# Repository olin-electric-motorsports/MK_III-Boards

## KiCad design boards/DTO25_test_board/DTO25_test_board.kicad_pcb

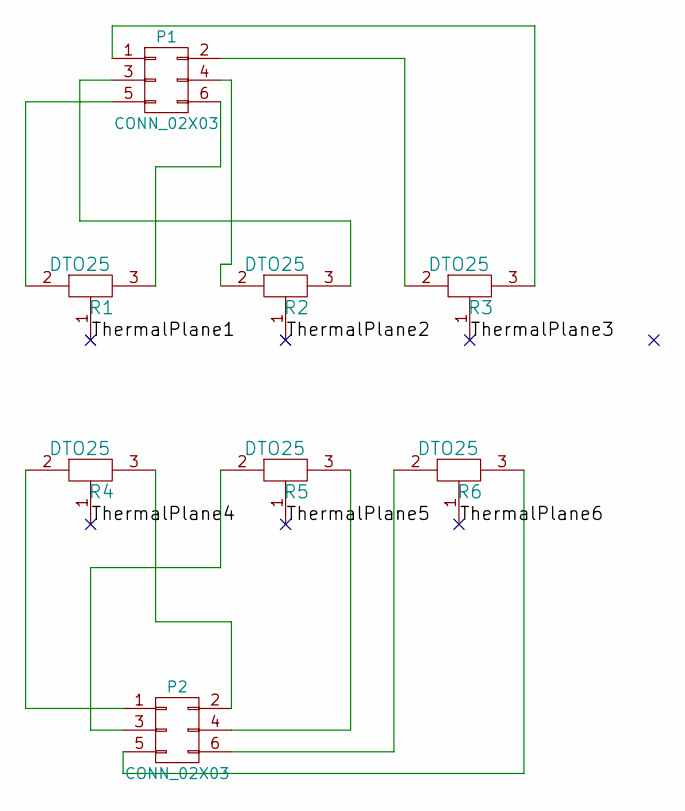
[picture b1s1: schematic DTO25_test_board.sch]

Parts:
P1, P2: CONN_02X03; Pin_Header_Straight_2x03; MPN 609-3234-ND
R1, R2, R3, R4, R5, R6: DTO25

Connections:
/ThermalPlane1: R1.1
/ThermalPlane2: R2.1
/ThermalPlane3: R3.1
/ThermalPlane4: R4.1
/ThermalPlane5: R5.1
/ThermalPlane6: R6.1
unnamed: P1.1, R3.3
unnamed: P1.2, R3.2
unnamed: P1.3, R2.3
unnamed: P1.4, R2.2
unnamed: P1.5, R1.2
unnamed: P1.6, R1.3
unnamed: P2.1, R4.2
unnamed: P2.2, R4.3
unnamed: P2.3, R5.2
unnamed: P2.4, R5.3
unnamed: P2.5, R6.3
unnamed: P2.6, R6.2

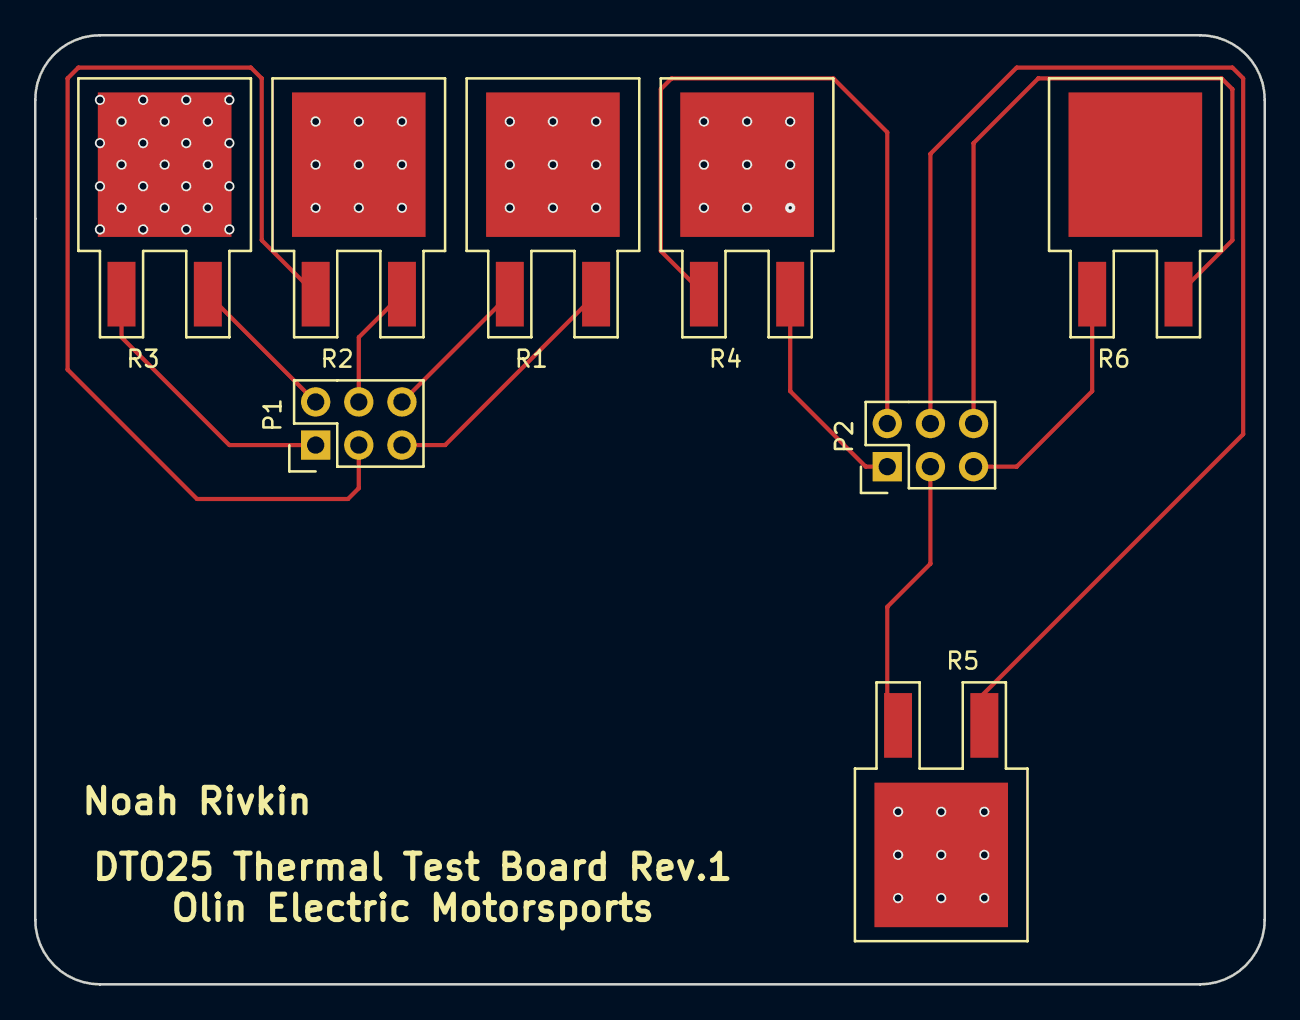
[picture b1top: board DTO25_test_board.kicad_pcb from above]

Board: 2 copper layers, 72.4 x 55.9 mm, 8 parts (0 on the bottom side), 12 nets.

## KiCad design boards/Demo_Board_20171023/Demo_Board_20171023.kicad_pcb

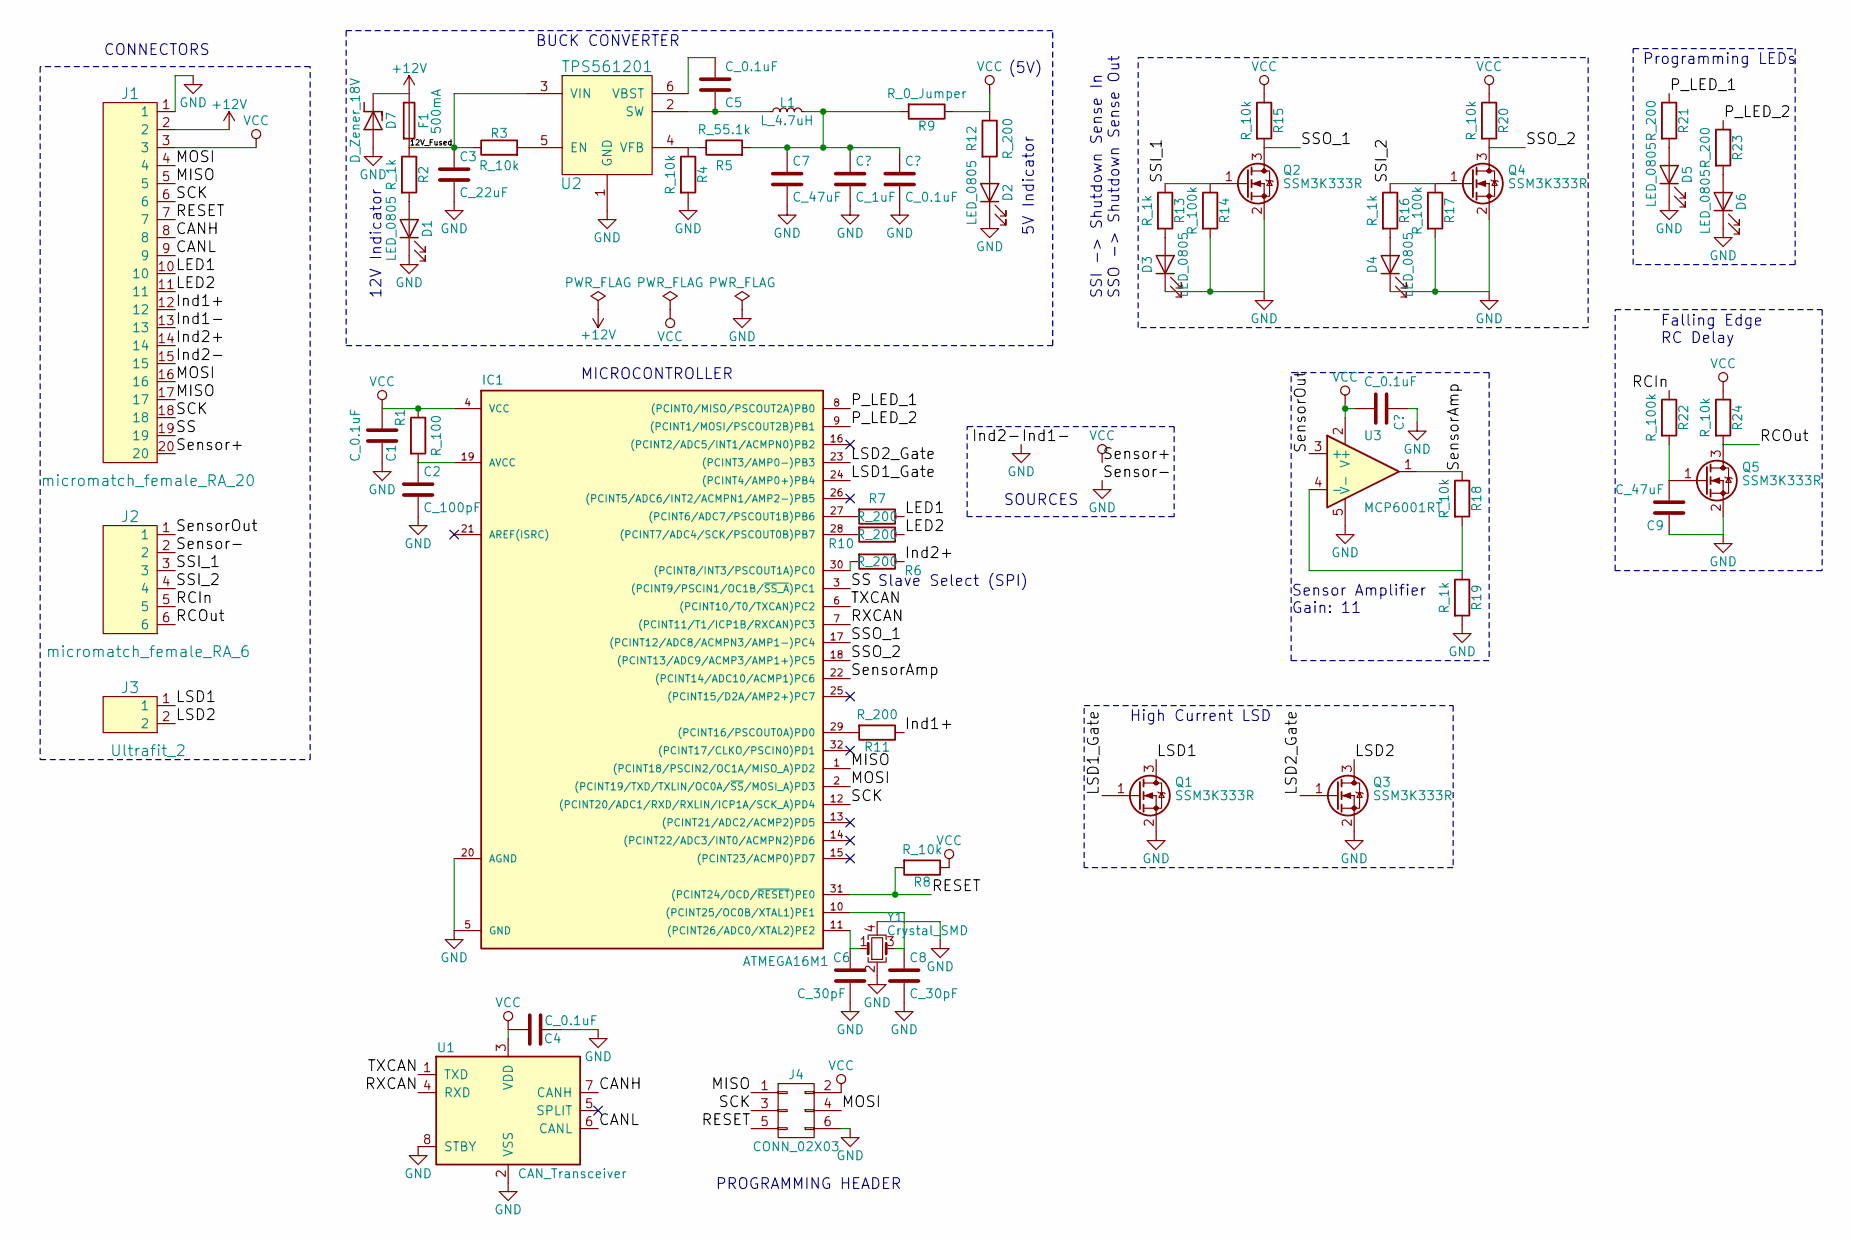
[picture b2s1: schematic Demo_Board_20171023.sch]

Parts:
C1, C4, C5: C_0.1uF; C_0805_OEM; MPN 478-3352-1-ND
C2: C_100pF; C_0805_OEM; MPN 399-1122-1-ND
C3: C_22uF; C_1206_OEM; MPN 1276-2725-1-ND
C6, C8: C_30pF; C_0805_OEM; MPN 1276-1130-1-ND
C7, C9: C_47uF; C_0805_OEM; MPN 587-4280-1-ND
D1, D2, D3, D4, D5, D6: LED_0805; LED_0805_OEM; MPN 475-1410-1-ND
D7: D_Zener_18V; DO-214AA; MPN SMBJ5355B-TPMSCT-ND
F1: 500mA; Fuse_1210; MPN 507-1786-1-ND
IC1: ATMEGA16M1; TQFP-32_7x7mm_Pitch0.8mm; MPN ATMEGA16M1-AU-ND
J1: micromatch_female_RA_20; micromatch_female_ra_20; MPN A99490CT-ND
J2: micromatch_female_RA_6; micromatch_female_ra_6; MPN A99483CT-ND
J3: Ultrafit_2; MPN WM11570-ND
J4: CONN_02X03; Pin_Header_Straight_2x03; MPN 609-3234-ND
L1: L_4.7uH; 4.7uH_Inductor_OEM; MPN 445-6583-1-ND
Q1, Q2, Q3, Q4, Q5: SSM3K333R; SOT-23F; MPN SSM3K333RLFCT-ND
R1: R_100; R_0805_OEM; MPN RNCP0805FTD100RCT-ND
R2, R13, R16, R19: R_1k; R_0805_OEM; MPN RNCP0805FTD1K00CT-ND
R3, R4, R8, R15, R18, R20, R24: R_10k; R_0805_OEM; MPN CRS0805-FX-1002ELFCT-ND
R5: R_55.1k; R_0805_OEM; MPN 311-51.1KCRCT-ND
R6, R7, R10, R11, R12, R21, R23: R_200; R_0805_OEM; MPN RMCF0805JT200RCT-ND
R9: R_0_Jumper; R_2512_OEM; MPN A121322CT-ND
R14, R17, R22: R_100k; R_0805_OEM; MPN 311-100KCRCT-ND
U1: CAN_Transceiver; SOIC-8_3.9x4.9mm_Pitch1.27mm_OEM; MPN MCP2561-E/SN-ND
U2: TPS561201; SOT-23-6_OEM; MPN TPS561201
U3: MCP6001RT; SOT-23-5_OEM; MPN MCP6001RT-I/OTCT-ND
Y1: Crystal_SMD; Crystal_SMD_FA238; MPN SER3686CT-ND

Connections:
+12V: D7.1 (K), F1.1, J1.2
/12V_Fused: C3.1, F1.2, R2.1, R3.1, U2.3 (VIN)
/CANH: J1.8, U1.7 (CANH)
/CANL: J1.9, U1.6 (CANL)
/Ind1+: J1.12, R11.1
/Ind2+: J1.14, R6.1
/LED1: J1.10, R7.1
/LED2: J1.11, R10.1
/LSD1: J3.1, Q1.3 (D)
/LSD1_Gate: IC1.24 ((PCINT4/AMP0+)PB4), Q1.1 (G)
/LSD2: J3.2, Q3.3 (D)
/LSD2_Gate: IC1.23 ((PCINT3/AMP0-)PB3), Q3.1 (G)
/MISO: IC1.1 ((PCINT18/PSCIN2/OC1A/MISO_A)PD2), J1.5, J1.17, J4.1
/MOSI: IC1.2 ((PCINT19/TXD/TXLIN/OC0A/~SS~/MOSI_A)PD3), J1.4, J1.16, J4.4
/P_LED_1: IC1.8 ((PCINT0/MISO/PSCOUT2A)PB0), R21.1
/P_LED_2: IC1.9 ((PCINT1/MOSI/PSCOUT2B)PB1), R23.1
/RCIn: J2.5, R22.1
/RCOut: J2.6, Q5.3 (D), R24.2
/RESET: IC1.31 ((PCINT24/OCD/~RESET~)PE0), J1.7, J4.5, R8.2
/RXCAN: IC1.7 ((PCINT11/T1/ICP1B/RXCAN)PC3), U1.4 (RXD)
/SCK: IC1.12 ((PCINT20/ADC1/RXD/RXLIN/ICP1A/SCK_A)PD4), J1.6, J1.18, J4.3
/SS: IC1.3 ((PCINT9/PSCIN1/OC1B/~SS_A~)PC1), J1.19
/SSI_1: J2.3, Q2.1 (G), R13.1, R14.1
/SSI_2: J2.4, Q4.1 (G), R16.1, R17.1
/SSO_1: IC1.17 ((PCINT12/ADC8/ACMPN3/AMP1-)PC4), Q2.3 (D), R15.2
/SSO_2: IC1.18 ((PCINT13/ADC9/ACMP3/AMP1+)PC5), Q4.3 (D), R20.2
/SensorAmp: IC1.22 ((PCINT14/ADC10/ACMP1)PC6), R18.1, U3.1
/SensorOut: J2.1, U3.3 (+)
/TXCAN: IC1.6 ((PCINT10/T0/TXCAN)PC2), U1.1 (TXD)
GND: C1.2, C2.2, C3.2, C4.2, C6.2, C7.2, C8.2, C9.1, D1.1 (K), D2.1 (K), D3.1 (K), D4.1 (K), D5.1 (K), D6.1 (K), D7.2 (A), IC1.5 (GND), IC1.20 (AGND), J1.1, J1.13, J1.15, J2.2, J4.6, Q1.2 (S), Q2.2 (S), Q3.2 (S), Q4.2 (S), Q5.2 (S), R4.2, R14.2, R17.2, R19.2, U1.2 (VSS), U1.8 (STBY), U2.1 (GND), U3.5 (V-), Y1.2, Y1.4
unnamed: C2.1, IC1.19 (AVCC), R1.2
unnamed: C5.1, U2.6 (VBST)
unnamed: C5.2, L1.1, U2.2 (SW)
unnamed: C6.1, IC1.11 ((PCINT26/ADC0/XTAL2)PE2), Y1.1
unnamed: C7.1, L1.2, R5.2, R9.2
unnamed: C8.1, IC1.10 ((PCINT25/OC0B/XTAL1)PE1), Y1.3
unnamed: C9.2, Q5.1 (G), R22.2
unnamed: D1.2 (A), R2.2
unnamed: D2.2 (A), R12.2
unnamed: D3.2 (A), R13.2
unnamed: D4.2 (A), R16.2
unnamed: D5.2 (A), R21.2
unnamed: D6.2 (A), R23.2
unnamed: IC1.27 ((PCINT6/ADC7/PSCOUT1B)PB6), R7.2
unnamed: IC1.28 ((PCINT7/ADC4/SCK/PSCOUT0B)PB7), R10.2
unnamed: IC1.29 ((PCINT16/PSCOUT0A)PD0), R11.2
unnamed: IC1.30 ((PCINT8/INT3/PSCOUT1A)PC0), R6.2
unnamed: R3.2, U2.5 (EN)
unnamed: R4.1, R5.1, U2.4 (VFB)
unnamed: R18.2, R19.1, U3.4 (-)
VCC: C1.1, C4.1, IC1.4 (VCC), J1.3, J1.20, J4.2, R1.1, R8.1, R9.1, R12.1, R15.1, R20.1, R24.1, U1.3 (VDD), U3.2 (V+)

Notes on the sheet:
BUCK CONVERTER
12V Indicator
5V Indicator
(5V)
MICROCONTROLLER
PROGRAMMING HEADER
SSI -> Shutdown Sense In SSO -> Shutdown Sense Out
Slave Select (SPI)
Programming LEDs
CONNECTORS
Falling Edge RC Delay
High Current LSD
Sensor Amplifier Gain: 11
SOURCES

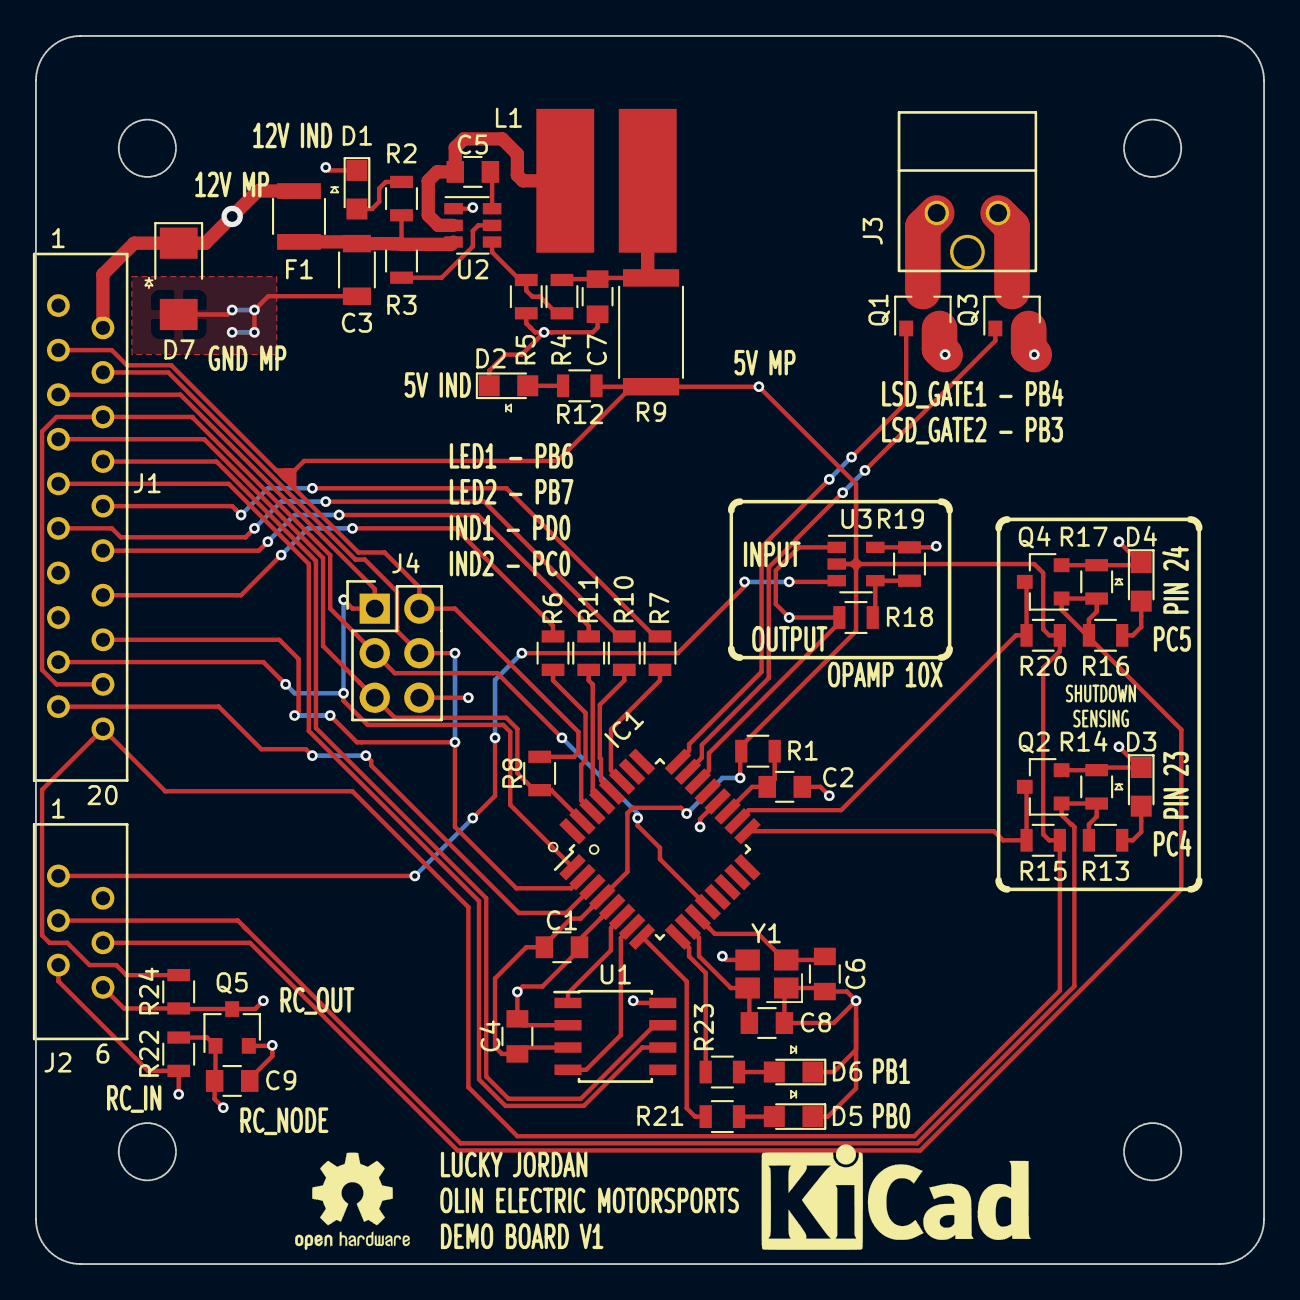
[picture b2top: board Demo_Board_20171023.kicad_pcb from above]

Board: 2 copper layers, 70.0 x 70.0 mm, 56 parts (0 on the bottom side), 51 nets.

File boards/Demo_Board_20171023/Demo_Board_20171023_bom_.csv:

Component,Description,Part,References,Value,Footprint,Quantity Per PCB,Datasheet,Package,MPN,MFN,PurchasingLink,Purchase_Link
1,Cap 50V 0.1uF 10% 0805,C_0.1uF,C1 C4 C5,C_0.1uF,C_0805_OEM,3,http://datasheets.avx.com/X7RDielectric.pdf,Value,478-3352-1-ND,Digi-Key,https://www.digikey.com/products/en?keywords=478-3352-1-ND,
2,Cap 50V 100pF 5% 0805,C_100pF,C2,C_100pF,C_0805_OEM,1,https://content.kemet.com/datasheets/KEM_C1003_C0G_SMD.pdf,Value,399-1122-1-ND,Digi-Key,https://www.digikey.com/product-detail/en/kemet/C0805C101J5G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,
3,Unpolarized capacitor,C_22uF,C3,C_22uF,C_1206_OEM,1,http://www.samsungsem.com/kr/support/product-search/mlcc/__i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,Value,1276-2725-1-ND,Digi-Key,https://www.digikey.com/products/en?keywords=1276-2725-1-ND,
4,Cap 50V 30pF 5% 0805,C_30pF,C6 C8,C_30pF,C_0805_OEM,2,https://media.digikey.com/pdf/Data%20Sheets/Samsung%20PDFs/C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,Value,1276-1130-1-ND,Digi-Key,https://www.digikey.com/product-detail/en/samsung-electro-me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,
5,CAP CER 47UF 6.3V X5R 0805,C_47uF,C7 C9,C_47uF,C_0805_OEM,2,http://www.yuden.co.jp/productdata/catalog/en/mlcc_all_e.pdf,Value,587-4280-1-ND,Digi-Key,https://www.digikey.com/product-detail/en/taiyo-yuden/JMK212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,
6,DIODE ZENER 18V 5W DO214AA,D_Zener_18V,D7,D_Zener_18V,DO-214AA,1,http://www.mccsemi.com/up_pdf/SMBJ5338B-SMBJ5388B(SMB).pdf,DO-214AA (SMB),SMBJ5355B-TPMSCT-ND,Digi-Key,https://www.digikey.com/products/en?keywords=SMBJ5355B-TPMSCT-ND,
7,LED_0805,LED_0805,D1 D2 D3 D4 D5 D6,LED_0805,LED_0805_OEM,6,http://www.osram-os.com/Graphics/XPic9/00078860_0.pdf,Value,475-1410-1-ND,Digi-Key,https://www.digikey.com/products/en?keywords=475-1410-1-ND,
8,PTC Fuse 16V 500mA,F_500mA_16V,F1,500mA,Fuse_1210,1,https://belfuse.com/resources/CircuitProtection/datasheets/0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,Value,507-1786-1-ND,Digi-Key,https://www.digikey.com/product-detail/en/bel-fuse-inc/0ZCH0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,
9,"TQFP32, 16k Flash, 1k SRAM, 512B EEPROM, CAN",ATMEGA16M1,IC1,ATMEGA16M1,TQFP-32_7x7mm_Pitch0.8mm,1,http://www.atmel.com/Images/Atmel-8209-8-bit%20AVR%20ATmega1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,Value,ATMEGA16M1-AU-ND,Digi-Key,https://www.digikey.com/product-detail/en/atmel/ATMEGA16M1-A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,
10,"Connector, double row, 02x03",CONN_02X03,J4,CONN_02X03,Pin_Header_Straight_2x03,1,http://portal.fciconnect.com/Comergent//fci/drawing/67996.pdf,Value,609-3234-ND,Digi-Key,https://www.digikey.com/product-detail/en/amphenol-fci/67997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,
11,ULTRAFIT CONN HDR 02CKT,Ultrafit_2,J3,Ultrafit_2,Ultrafit_2,1,,Value,WM11570-ND,Digi-Key,https://www.digikey.com/product-detail/en/molex-llc/17228611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,
12,connector micromatch female RA 20,micromatch_female_RA_20,J1,micromatch_female_RA_20,micromatch_female_ra_20,1,,Value,A99490CT-ND,Digi-Key,https://www.digikey.com/product-detail/en/te-connectivity-am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,
13,connector micromatch female RA 6,micromatch_female_RA_6,J2,micromatch_female_RA_6,micromatch_female_ra_6,1,,Value,A99483CT-ND,Digi-Key,https://www.digikey.com/product-detail/en/te-connectivity-am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,
14,Inductor 4.7uH 4.4A,L_4.7uH,L1,L_4.7uH,4.7uH_Inductor_OEM,1,https://product.tdk.com/info/en/documents/wdcatalog/withdraw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,Value,445-6583-1-ND,Digi-Key,https://www.digikey.com/product-detail/en/tdk-corporation/VL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,
15,"60V Vds, 0.115A Id, N-channel MOSFET, SOT-23",SSM3K333R,Q1 Q2 Q3 Q4 Q5,SSM3K333R,SOT-23F,5,https://drive.google.com/drive/folders/0B-V-iZf33Y4GNzhDQTJZanJRbVk,SOT-23-3 Flat Leads,SSM3K333RLFCT-ND,Digi-Key,https://www.digikey.com/product-detail/en/toshiba-semiconduc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,https://www.digikey.com/product-detail/en/toshiba-semiconduc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
16,Res 0 2512 3W Jumper,R_0_Jumper,R9,R_0_Jumper,R_2512_OEM,1,http://www.te.com/commerce/DocumentDelivery/DDEController?Ac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,Value,A121322CT-ND,Digi-Key,https://www.digikey.com/products/en?keywords=A121322CT-ND,
17,Res 100 1%,R_100,R1,R_100,R_0805_OEM,1,https://www.seielect.com/Catalog/SEI-rncp.pdf,Value,RNCP0805FTD100RCT-ND,Digi-Key,https://www.digikey.com/products/en?keywords=RNCP0805FTD100RCT-ND,
18,Res 100k 1%,R_100k,R14 R17 R22,R_100k,R_0805_OEM,3,http://www.yageo.com.tw/exep/pages/download/literatures/PYu-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,Value,311-100KCRCT-ND,Digi-Key,https://www.digikey.com/products/en?keywords=311-100KCRCT-ND,
19,Res 10k 1%,R_10k,R3 R4 R8 R15 R18 R20 R24,R_10k,R_0805_OEM,7,http://www.bourns.com/data/global/pdfs/CRS.pdf,Value,CRS0805-FX-1002ELFCT-ND,Digi-Key,https://www.digikey.com/products/en?keywords=CRS0805-FX-1002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,
20,Res 1k 1%,R_1k,R2 R13 R16 R19,R_1k,R_0805_OEM,4,https://www.seielect.com/Catalog/SEI-rncp.pdf,Value,RNCP0805FTD1K00CT-ND,Digi-Key,https://www.digikey.com/products/en?keywords=RNCP0805FTD1K00CT-ND,
21,Res 200 5%,R_200,R6 R7 R10 R11 R12 R21 R23,R_200,R_0805_OEM,7,https://www.seielect.com/Catalog/SEI-RMCF_RMCP.pdf,Value,RMCF0805JT200RCT-ND,Digi-Key,https://www.digikey.com/products/en?keywords=RMCF0805JT200RCT-ND,
22,Res 55.1k 1%,R_55.1k,R5,R_55.1k,R_0805_OEM,1,http://www.yageo.com.tw/exep/pages/download/literatures/PYu-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,Value,311-51.1KCRCT-ND,Digi-Key,https://www.digikey.com/products/en?keywords=311-51.1KCRCT-ND,
23,"High-Speed CAN Transceiver, 1Mbps, 5V supply, SPLIT pin, -40C to +125C, SOIC8 package",CAN_Transceiver,U1,CAN_Transceiver,SOIC-8_3.9x4.9mm_Pitch1.27mm_OEM,1,http://www.microchip.com/mymicrochip/filehandler.aspx?ddocna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,Value,MCP2561-E/SN-ND,Digi-Key,https://www.digikey.com/products/en?keywords=mcp2561-e%2Fsn,
24,IC OPAMP GP 1MHZ RRO SOT23-5  1.8-6V,MCP6001RT,U3,MCP6001RT,SOT-23-5_OEM,1,http://ww1.microchip.com/downloads/en/DeviceDoc/21733j.pdf,,MCP6001RT-I/OTCT-ND,Digi-Key,https://www.digikey.com/product-detail/en/microchip-technolo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,
25,4.5V - 17V Input 1A Synchronous Buck Converter,TPS561201,U2,TPS561201,SOT-23-6_OEM,1,http://www.ti.com/lit/ds/symlink/tps561201.pdf,Value,TPS561201,Digi-Key,https://www.digikey.com/products/en?keywords=296-46928-1-ND,
26,"Two pin crystal, two ground/package pins (pin2 and 3) small symbol",Crystal_SMD,Y1,Crystal_SMD,Crystal_SMD_FA238,1,https://support.epson.biz/td/api/doc_check.php?dl=brief_FA-2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,Value,SER3686CT-ND,Digi-Key,https://www.digikey.com/products/en?keywords=SER3686CT-ND,





Component Groups:,26
Component Count:,56
Fitted Components:,56
Number of PCBs:,1
Total components:,56
Schematic Version:,
Schematic Date:,
BoM Date:,11/30/2017 12:03:13 AM
Schematic Source:,C:/Users/ljordan/Desktop/Olin/Formula/2017-18/MK_III-Boards/boards/Demo_Board_20171023/Demo_Board_20171023.sch
KiCad Version:,Eeschema 4.0.7

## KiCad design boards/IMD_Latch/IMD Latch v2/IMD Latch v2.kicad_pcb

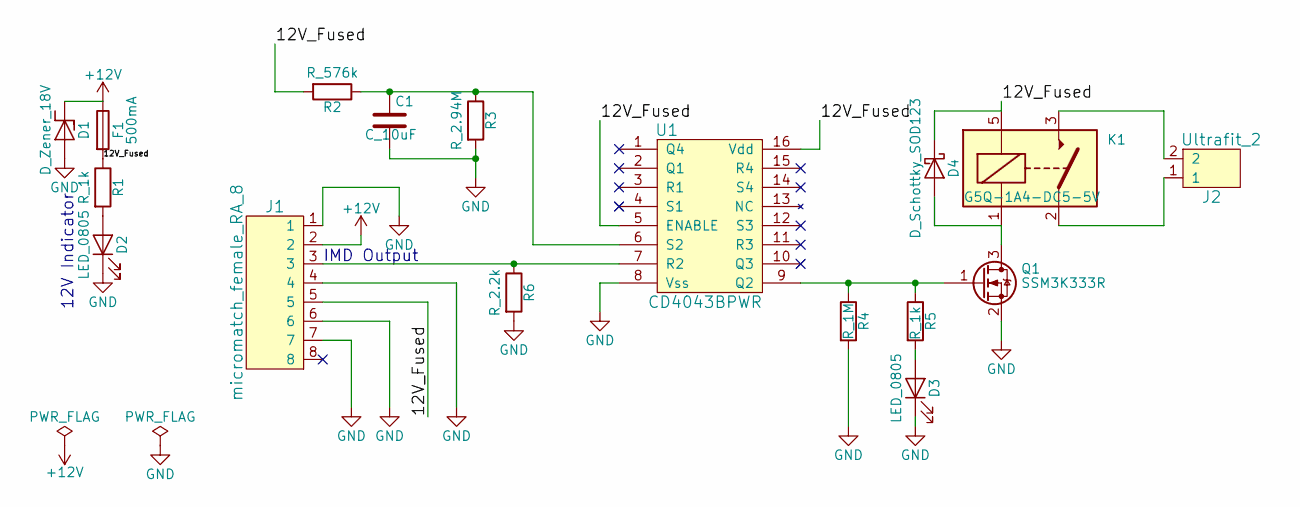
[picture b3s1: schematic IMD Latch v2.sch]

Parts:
C1: C_10uF; C_0805_OEM; MPN 478-5167-1-ND
D1: D_Zener_18V; DO-214AA; MPN SMBJ5355B-TPMSCT-ND
D2, D3: LED_0805; LED_0805_OEM; MPN 475-1410-1-ND
D4: D_Schottky_SOD123; D_SOD-123W_OEM; MPN 1727-2394-1-ND
F1: 500mA; Fuse_1210; MPN 507-1786-1-ND
J1: micromatch_female_RA_8; micromatch_female_ra_8; MPN A99484CT-ND
J2: Ultrafit_2; MPN WM11570-ND
K1: G5Q-1A4-DC5-5V; Relay_SPST_OMRON-G5Q-1A4_OEM; MPN Z3632-ND
Q1: SSM3K333R; SOT-23F; MPN SSM3K333RLFCT-ND
R1, R5: R_1k; R_0805_OEM; MPN RNCP0805FTD1K00CT-ND
R2: R_576k; R_0805_OEM; MPN 541-576KCCT-ND
R3: R_2.94M; R_0805_OEM; MPN 541-2.94MCCT-ND
R4: R_1M; R_0805_OEM; MPN RMCF0805JT1M00CT-ND
R6: R_2.2k; R_0805_OEM; MPN RMCF0805FT2K20CT-ND
U1: CD4043BPWR; TSSOP-16-OEM; MPN 296-14106-1-ND

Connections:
+12V: D1.1 (K), F1.1, J1.2
/12V_Fused: D4.1 (K), F1.2, J1.5, K1.5, R1.1, R2.2, U1.5 (ENABLE), U1.16 (Vdd)
GND: C1.2, D1.2 (A), D2.1 (K), D3.1 (K), J1.1, J1.4, J1.6, J1.7, Q1.2 (S), R3.2, R4.2, R6.2, U1.8 (Vss)
unnamed: C1.1, R2.1, R3.1, U1.6 (S2)
unnamed: D2.2 (A), R1.2
unnamed: D3.2 (A), R5.2
unnamed: D4.2 (A), K1.1, Q1.3 (D)
unnamed: J1.3, R6.1, U1.7 (R2)
unnamed: J2.1, K1.2
unnamed: J2.2, K1.3
unnamed: Q1.1 (G), R4.1, R5.1, U1.9 (Q2)

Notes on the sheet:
12V Indicator
IMD Output

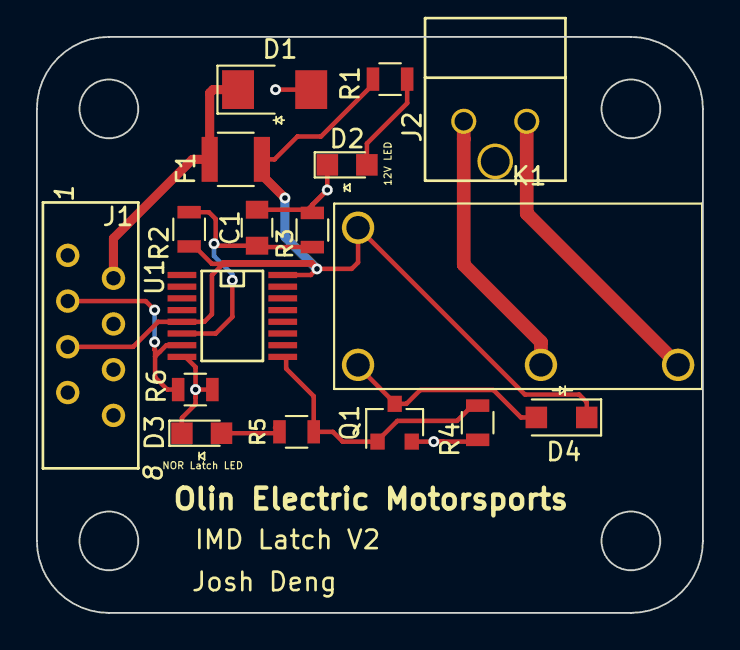
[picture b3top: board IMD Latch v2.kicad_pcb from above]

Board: 2 copper layers, 37.0 x 32.0 mm, 17 parts (0 on the bottom side), 11 nets.

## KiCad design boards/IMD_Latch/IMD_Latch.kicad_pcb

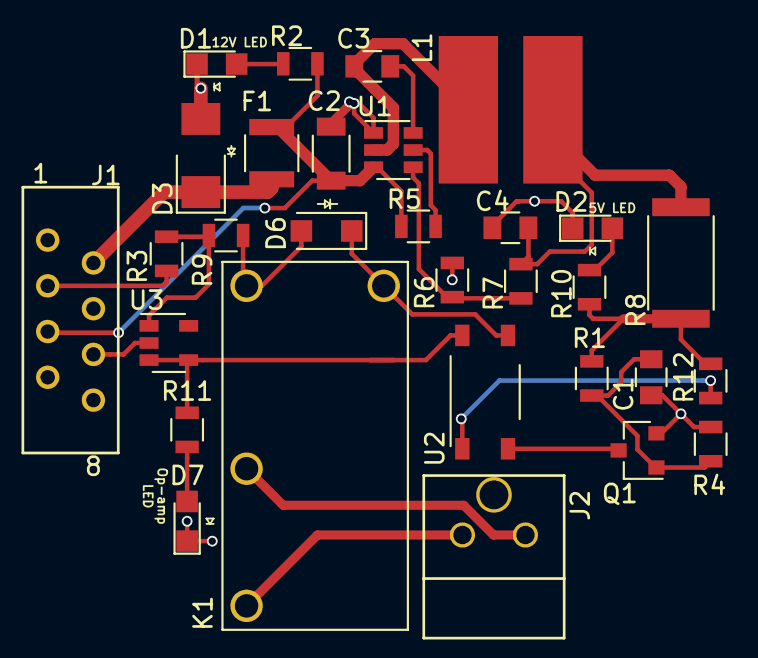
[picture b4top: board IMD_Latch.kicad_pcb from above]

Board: 2 copper layers, 30 parts (0 on the bottom side), 21 nets.

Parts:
C1: C_10uF; C_0805_OEM
C2: C_22uF; C_1206_OEM
C3: C_0.1uF; C_0805_OEM
C4: C_47uF; C_0805_OEM
D1, D2, D7: LED_0805; LED_0805_OEM
D3: D_Zener_18V; DO-214AA
D6: D_Schottky_SOD123; D_SOD-123W_OEM
F1: F_500mA_16V; Fuse_1210
J1: micromatch_female_RA_8; micromatch_female_ra_8
J2: Ultrafit_2
K1: G5Q-1A4-DC5-5V; Relay_SPST_OMRON-G5Q-1A4_OEM
L1: L_4.7uH; 4.7uH_Inductor_OEM
Q1: SSM3K333R; SOT-23F
R1, R4: R_402k; R_0805_OEM
R2, R12: R_1k; R_0805_OEM
R3: R_1.07k; R_0805_OEM
R5, R6: R_10k; R_0805_OEM
R7: R_55.1k; R_0805_OEM
R8: R_0_Jumper; R_2512_OEM
R9: R_1.13k; R_0805_OEM
R10, R11: R_200; R_0805_OEM
U1: TPS561201; SOT-23-6_OEM
U2: TLP175A_OEM; MFSOP6-4_4.4x3.6mm_Pitch1.27mm_OEM
U3: TS507IYLT; SOT-23-5_OEM

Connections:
+12V: D3.1, F1.1, J1.2
/12V_Fused: C2.1, F1.2, J1.5, R2.1, R5.1, U1.3
GND: C1.2, C2.2, C4.2, D1.1, D2.1, D3.2, D6.2, D7.1, J1.1, J1.4, J1.6, J1.7, K1.1, Q1.2, R4.2, R6.2, R9.1, U1.1, U3.2
unnamed: C1.1, Q1.1, R1.2, R4.1
unnamed: C3.1, U1.6
unnamed: C3.2, L1.1, U1.2
unnamed: C4.1, L1.2, R7.2, R8.2
unnamed: D1.2, R2.2
unnamed: D2.2, R10.2
unnamed: D6.1, K1.5, U2.4
unnamed: D7.2, R11.2
unnamed: J1.3, R3.1
unnamed: J2.1, K1.2
unnamed: J2.2, K1.3
unnamed: Q1.3, U2.3
unnamed: R3.2, R9.2, U3.1
unnamed: R5.2, U1.5
unnamed: R6.1, R7.1, U1.4
unnamed: R11.1, U2.6, U3.3, U3.4
unnamed: R12.1, U2.1
VCC: R1.1, R8.1, R10.1, R12.2, U3.5

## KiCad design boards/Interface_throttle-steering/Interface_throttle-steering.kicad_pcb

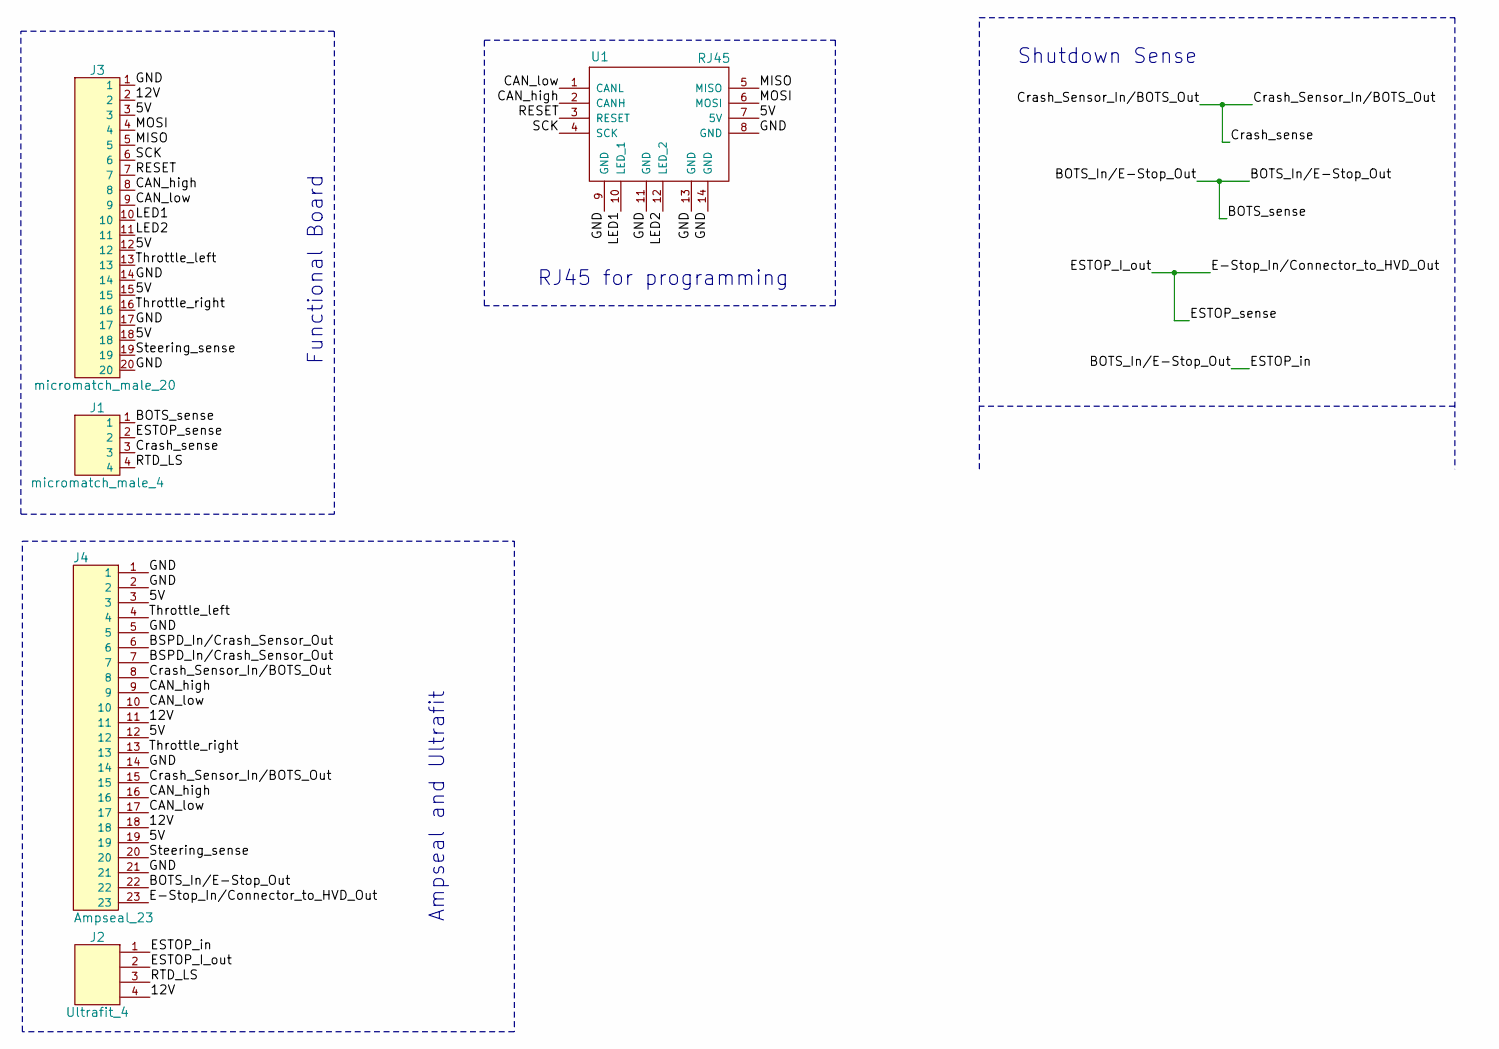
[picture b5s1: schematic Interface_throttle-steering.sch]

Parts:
J1: micromatch_male_4; micromatch_female_ra_4; MPN A107034CT-ND
J2: Ultrafit_4; MPN WM11574-ND
J3: micromatch_male_20; micromatch_female_ra_20; MPN A111126CT-ND
J4: Ampseal_23
U1: RJ45; RJ45-Vertical

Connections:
/5V: J3.3, J3.12, J3.15, J3.18, J4.3, J4.12, J4.19, U1.7 (5V)
/12V: J2.4, J3.2, J4.11, J4.18
/BOTS_In/E-Stop_Out: J1.1, J2.1, J4.22
/BSPD_In/Crash_Sensor_Out: J4.6, J4.7
/CAN_high: J3.8, J4.9, J4.16, U1.2 (CANH)
/CAN_low: J3.9, J4.10, J4.17, U1.1 (CANL)
/Crash_Sensor_In/BOTS_Out: J1.3, J4.8, J4.15
/E-Stop_In/Connector_to_HVD_Out: J1.2, J2.2, J4.23
/GND: J3.1, J3.14, J3.17, J3.20, J4.1, J4.2, J4.5, J4.14, J4.21, U1.8 (GND), U1.9 (GND), U1.11 (GND), U1.13 (GND), U1.14 (GND)
/LED1: J3.10, U1.10 (LED_1)
/LED2: J3.11, U1.12 (LED_2)
/MISO: J3.5, U1.5 (MISO)
/MOSI: J3.4, U1.6 (MOSI)
/RESET: J3.7, U1.3 (RESET)
/RTD_LS: J1.4, J2.3
/SCK: J3.6, U1.4 (SCK)
/Steering_sense: J3.19, J4.20
/Throttle_left: J3.13, J4.4
/Throttle_right: J3.16, J4.13

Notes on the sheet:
Shutdown Sense
Functional Board
Ampseal and Ultrafit
RJ45 for programming

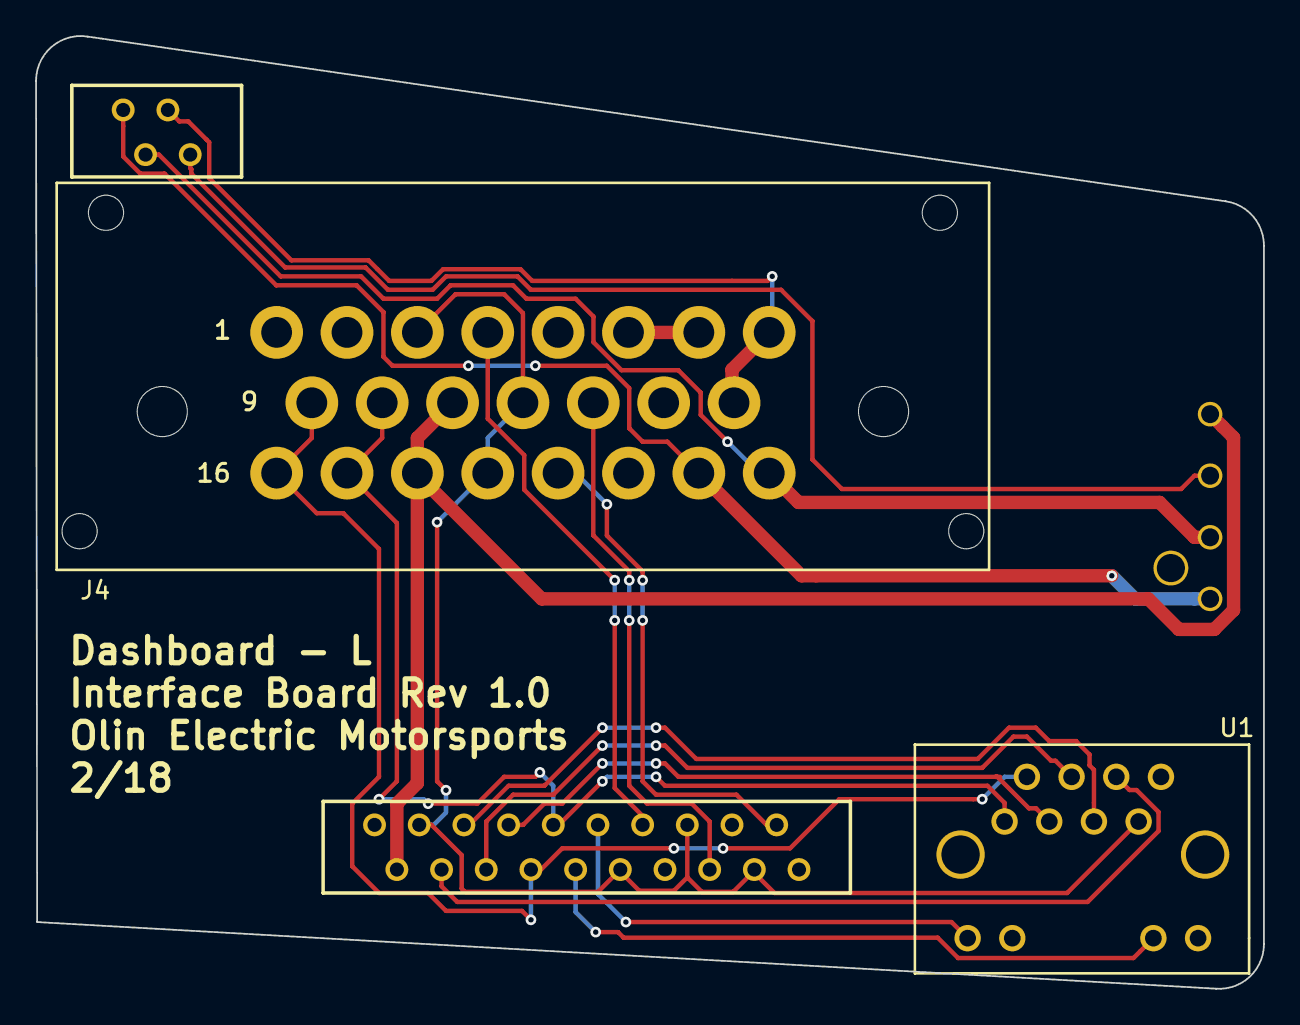
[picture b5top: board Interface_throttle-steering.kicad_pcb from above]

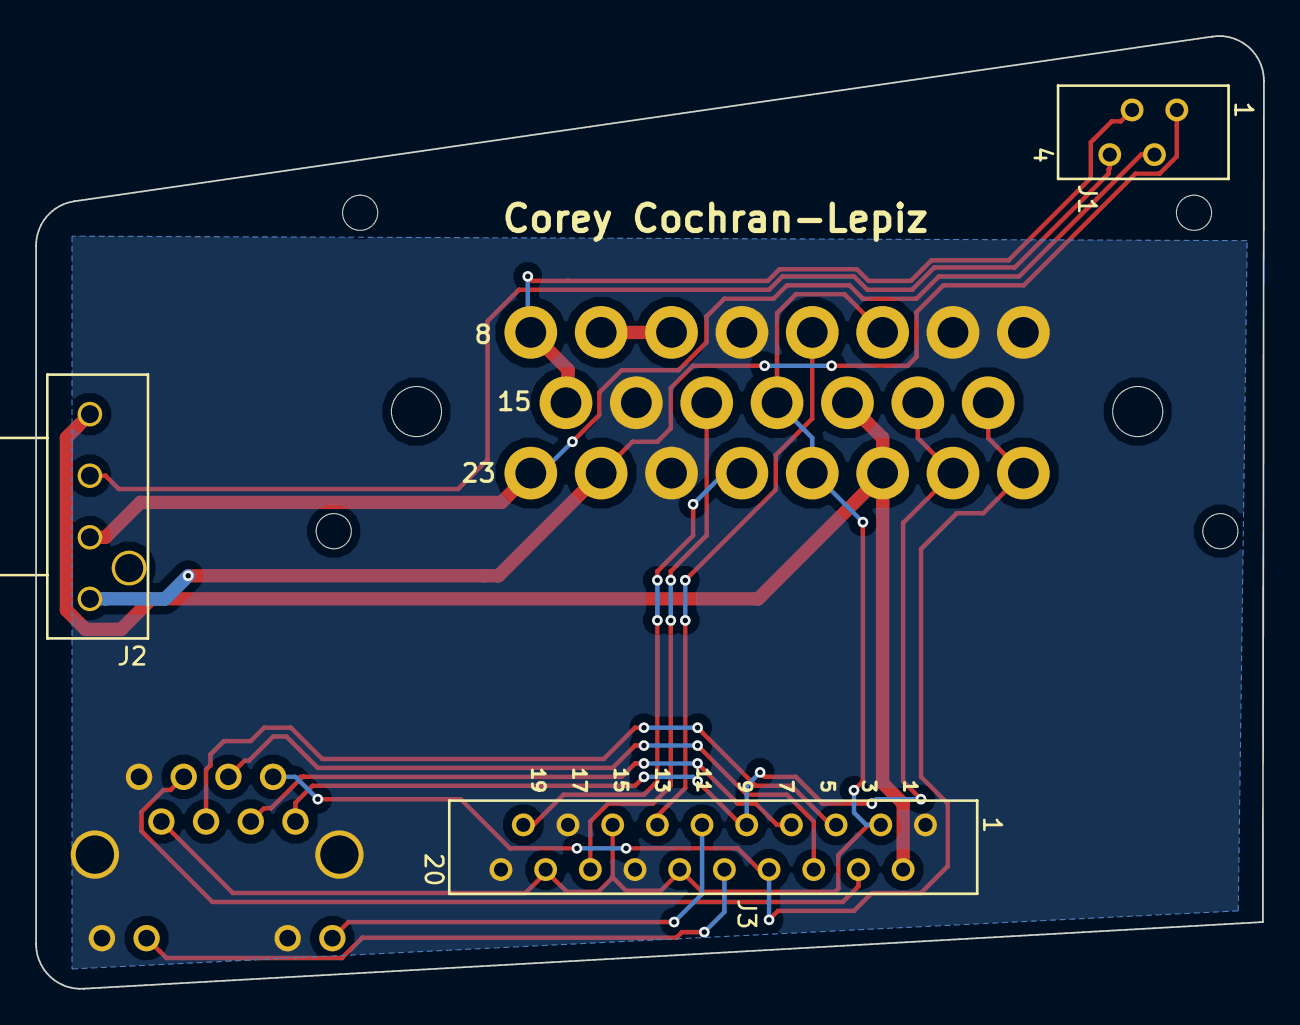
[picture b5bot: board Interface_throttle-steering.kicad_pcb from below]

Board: 2 copper layers, 69.8 x 54.2 mm, 5 parts (3 on the bottom side), 19 nets.

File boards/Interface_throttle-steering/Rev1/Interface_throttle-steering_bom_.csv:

Component,Description,Part,References,Value,Footprint,Quantity Per PCB,Datasheet,PurchasingLink2,Package,MPN,MFN,MPN2,PurchasingLink
1,Waterproof Panel-Mount Connector RA 23-Pin,Ampseal_23,J4,Ampseal_23,Ampseal_23,1,,,,,,,
2,Ultrafit 4 Pin Connector,Ultrafit_4,J2,Ultrafit_4,Ultrafit_4,1,http://www.literature.molex.com/SQLImages/kelmscott/Molex/PD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,https://www.digikey.com/product-detail/en/molex-llc/17225610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,Value,WM11574-ND,Digi-Key,WM11564-ND,https://www.digikey.com/products/en?keywords=WM11574-ND
3,connector micromatch male 20,micromatch_male_20,J3,micromatch_male_20,micromatch_female_ra_20,1,,,Value,A111126CT-ND,Digi-Key,,https://www.digikey.com/product-detail/en/te-connectivity-am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
4,connector micromatch male 4,micromatch_male_4,J1,micromatch_male_4,micromatch_female_ra_4,1,,,Value,A107034CT-ND,Digi-Key,,https://www.digikey.com/product-detail/en/te-connectivity-am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
5,,RJ45,U1,RJ45,RJ45-Vertical,1,,,,,,,





Component Groups:,5
Component Count:,5
Fitted Components:,5
Number of PCBs:,1
Total components:,5
Schematic Version:,
Schematic Date:,
BoM Date:,Mon 12 Feb 2018 08:14:13 PM EST
Schematic Source:,/home/corey/Desktop/Formula/MK_III-Boards/boards/Interface_throttle-steering/Interface_throttle-steering.sch
KiCad Version:,Eeschema 4.0.7-e2-6376~58~ubuntu16.04.1
